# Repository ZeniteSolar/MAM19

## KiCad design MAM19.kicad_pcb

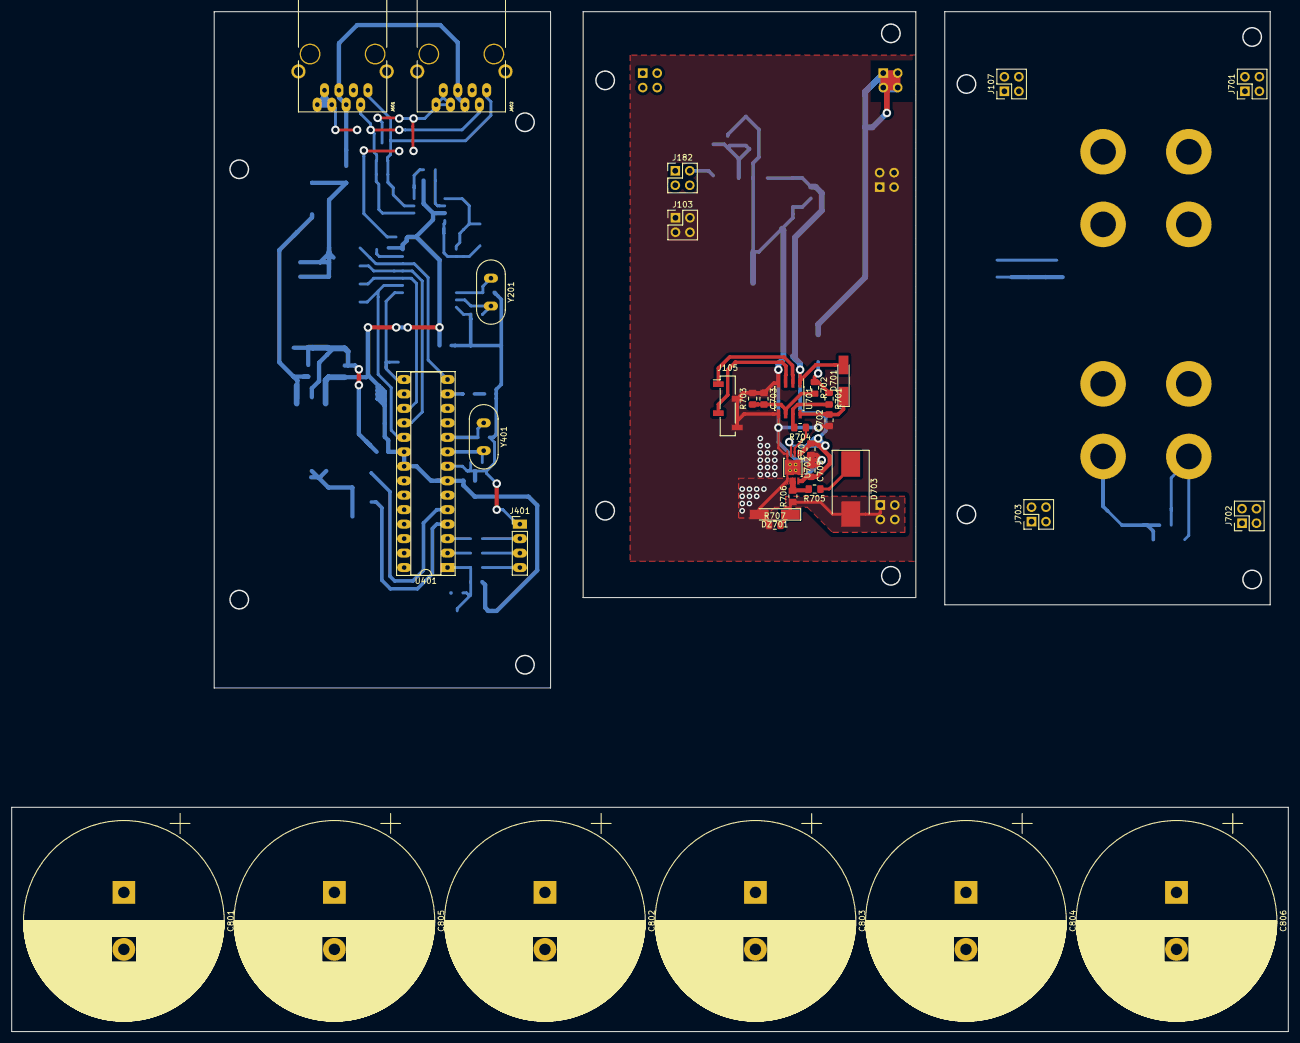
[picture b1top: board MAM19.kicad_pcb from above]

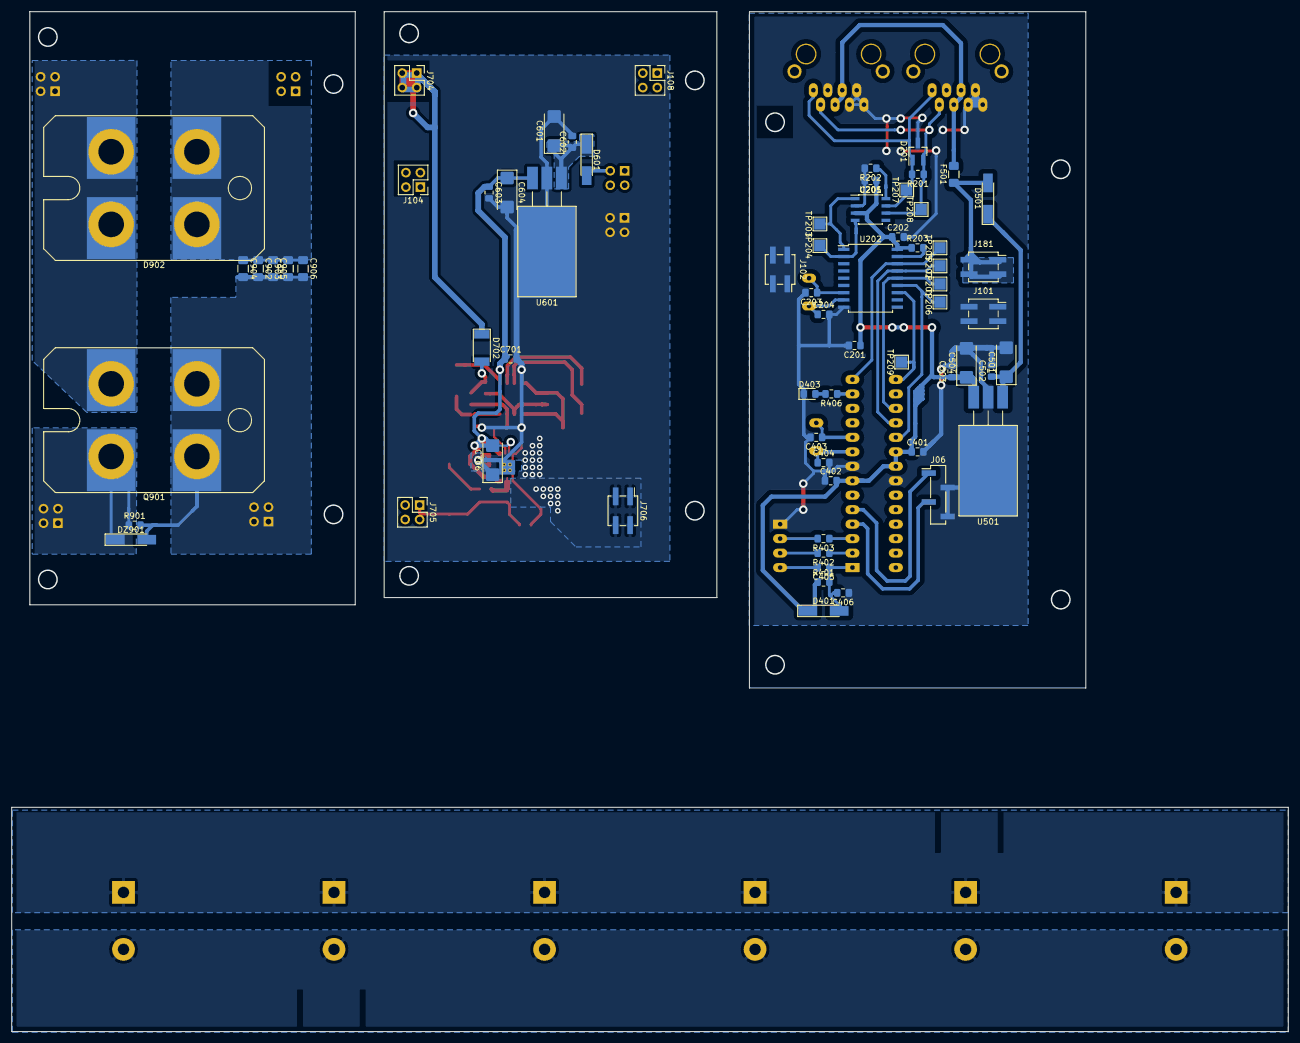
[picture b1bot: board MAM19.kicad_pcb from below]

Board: 2 copper layers, 224.2 x 179.1 mm, 101 parts (66 on the bottom side), 45 nets.

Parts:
C201, C202, C205, C401, C402, C405, C406, C502, C503, C602, C603, C701, C702, C703, C704: 100nF; C_0805_2012Metric_Pad1.15x1.40mm_HandSolder
C203, C204, C403, C404: 22pF; C_0805_2012Metric_Pad1.15x1.40mm_HandSolder
C501, C504, C601, C604: 1uF; CP_EIA-6032-20_AVX-F_Pad2.25x2.35mm_HandSolder
C705: 1uF; C_0805_2012Metric_Pad1.15x1.40mm_HandSolder
C706: 10uF; CP_EIA-6032-20_AVX-F_Pad2.25x2.35mm_HandSolder
C801, C802, C803, C804, C805, C806: 4700uF; CP_Radial_D35.0mm_P10.00mm_SnapIn
C902, C903, C904, C905, C906: 10nF 250V; C_1206_3216Metric_Pad1.42x1.75mm_HandSolder
D201: pesd1can; SOT-23_Handsoldering
D401, D501, D601: LL4148; D_MiniMELF_Handsoldering
D403: LED_RED; LED_0805_2012Metric_Pad1.15x1.40mm_HandSolder
D701: BAV102; D_MiniMELF_Handsoldering
D702: BYD77; D_MELF
D703: ES3B; D_SMC_Handsoldering
D902: DSEI2x101; SOT-227
DZ701, DZ901: 15V; D_MiniMELF_Handsoldering
F501: 500mA; Fuse_1206_3216Metric_Pad1.42x1.75mm_HandSolder
J06: PWM/IR C; PinHeader_1x04_P2.54mm_Vertical_SMD_Pin1Left
J101: GNDC1; PinSocket_2x02_P2.54mm_Vertical_SMD
J102: GNDC2; PinSocket_2x02_P2.54mm_Vertical_SMD
J103: GNDD1; PinHeader_2x02_P2.54mm_Vertical
J104: GNDD2; PinHeader_2x02_P2.54mm_Vertical
J105: PWM/IR D; PinSocket_1x04_P2.54mm_Vertical_SMD_Pin1Left
J107: HOLD1; PinHeader_2x02_P2.54mm_Vertical
J108: HOLD2; PinHeader_2x02_P2.54mm_Vertical
J181: +18C; PinSocket_2x02_P2.54mm_Vertical_SMD
J182: +18D; PinHeader_2x02_P2.54mm_Vertical
J401: USART; PinHeader_1x04_P2.54mm_Vertical
J601, J602: RJ45; RJ45_YH59_01
J701: DRAIND; PinHeader_2x02_P2.54mm_Vertical
J702: GATED; PinHeader_2x02_P2.54mm_Vertical
J703: SOURCED; PinHeader_2x02_P2.54mm_Vertical
J704: DRAINCH; PinHeader_2x02_P2.54mm_Vertical
J705: GATECH; PinHeader_2x02_P2.54mm_Vertical
J706: SOURCECH; PinHeader_2x02_P2.54mm_Vertical_SMD
Q901: IXFN420N10T; SOT-227
R201: 120; R_0805_2012Metric_Pad1.15x1.40mm_HandSolder
R202: 4k7; R_0805_2012Metric_Pad1.15x1.40mm_HandSolder
R203, R401: 10k; R_0805_2012Metric_Pad1.15x1.40mm_HandSolder
R402, R403: 1k; R_0805_2012Metric_Pad1.15x1.40mm_HandSolder
R406: 330; R_0805_2012Metric_Pad1.15x1.40mm_HandSolder
R701: 22K; R_0805_2012Metric_Pad1.15x1.40mm_HandSolder
R702, R707, R901: 10K; R_0805_2012Metric_Pad1.15x1.40mm_HandSolder
R703: 820; R_0805_2012Metric_Pad1.15x1.40mm_HandSolder
R704: 0; R_0805_2012Metric_Pad1.15x1.40mm_HandSolder
R705: 4R7; R_0805_2012Metric_Pad1.15x1.40mm_HandSolder
R706: 10; R_0805_2012Metric_Pad1.15x1.40mm_HandSolder
TP201: SI; TestPoint_Pad_2.0x2.0mm
TP202: SO; TestPoint_Pad_2.0x2.0mm
TP203: TXCAN; TestPoint_Pad_2.0x2.0mm
TP204: RXCAN; TestPoint_Pad_2.0x2.0mm
TP205: SC; TestPoint_Pad_2.0x2.0mm
TP206: SCK; TestPoint_Pad_2.0x2.0mm
TP207: CAN_H; TestPoint_Pad_2.0x2.0mm
TP208: CAN_L; TestPoint_Pad_2.0x2.0mm
TP209: INT; TestPoint_Pad_2.0x2.0mm
U201: MCP2551-I/SN; SOIC-8_3.9x4.9mm_P1.27mm
U202: MCP2515-xSO; SOIC-18W_7.5x11.6mm_P1.27mm
U401: ATMEGA328P-PU; DIP-28_W7.62mm_Socket
U501: LM7805; TO-220-3_Horizontal_TabDown_SMD
U601: LM7815; TO-220-3_Horizontal_TabDown_SMD
U701: IR2127S; SOIC-8_3.9x4.9mm_P1.27mm
U702: UCC2732; MSOP-8-1EP_3x3mm_P0.65mm_EP2.54x2.8mm_ThermalVias
Y201, Y401: 16MHz; Crystal_HC49-U_Vertical

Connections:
+5V: C201.1, C202.1, C205.1, C401.1, C402.2, C503.1, C504.1, D401.1, R203.1, R401.1, U201.3, U202.18, U401.7, U401.20, U401.21, U501.3
+15V: C603.1, C604.1, C701.1, C704.2, C705.2, C706.2, D701.2, U601.3, U701.1, U702.1, U702.3, U702.8
+36V: C801.1, C802.1, C803.1, C804.1, C805.1, C806.1, C902.1, C903.2, C904.1, C905.1, C906.1, D902.1, D902.4
/CANBUS CONN/CAN_18V: F501.2, J601.4, J601.5, J602.4, J602.5
/CANBUS CONN/CAN_H: D201.1, J601.1, J602.1, R201.2, TP207.1, U201.7
/CANBUS CONN/CAN_L: D201.2, J601.2, J602.2, R201.1, TP208.1, U201.6
/CANBUS/CS: TP205.1, U202.16, U401.14
/CANBUS/INT: TP209.1, U202.12, U401.15
/CANBUS/RXCAN: TP204.1, U201.4, U202.2
/CANBUS/TXCAN: TP203.1, U201.1, U202.1
/MCU/IR_2127_FAULT: J06.3, U401.4
/MCU/PWM: J06.1, U401.5
/MCU/RESET: C405.1, C406.2, D401.2, R401.2, U401.1
/MCU/USART_RX: R402.1, U401.2
/MCU/USART_TX: R403.1, U401.3
/MISO: TP202.1, U202.15, U401.18
/MOSI: TP201.1, U202.14, U401.17
/POWER SUPPLY +15V/+18V_IN: D501.2, D601.2, F501.1, J181.1, J181.2, J181.3, J181.4, J182.1, J182.2, J182.3, J182.4
/SCK: TP206.1, U202.13, U401.19
/chopper/-MOTOR: D702.1, D902.2, D902.3, J701.1, J701.2, J701.3, J701.4, J704.1, J704.2, J704.3, J704.4, Q901.3
/chopper/GATE: D703.2, DZ701.1, DZ901.1, J702.1, J702.2, J702.3, J702.4, J705.1, J705.2, J705.3, J705.4, Q901.2, R706.1, R707.2, R901.1
/driver/IR2127_FAULT: J105.3, U701.3
/driver/PWM: J105.1, U701.2
GND: C201.2, C202.2, C203.2, C204.2, C205.2, C401.2, C402.1, C403.2, C404.2, C406.1, C501.2, C502.2, C503.2, C504.2, C601.2, C602.2, C603.2, C604.2, C701.2, C702.1, C703.1, C704.1, C705.1, C706.1, C801.2, C802.2, C803.2, C804.2, C805.2, C806.2, C902.2, C903.1, C904.2, C905.2, C906.2, D201.3, D403.1, DZ701.2, DZ901.2, J06.2, J06.4, J101.1, J101.2, J101.3, J101.4, J102.1, J102.2, J102.3, J102.4, J103.1, J103.2, J103.3, J103.4, J104.1, J104.2, J104.3, J104.4, J105.2, J105.4, J401.1, J601.3, J601.6, J601.7, J601.8, J602.3, J602.6, J602.7, J602.8, J703.1, J703.2, J703.3, J703.4, J706.1, J706.2, J706.3, J706.4, Q901.1, Q901.4, R202.2, R703.2, R707.1, R901.2, U201.2, U202.9, U401.8, U401.22, U501.2, U601.2, U701.4, U701.5, U702.4, U702.5
unnamed: C203.1, U202.7, Y201.1
unnamed: C204.1, U202.8, Y201.2
unnamed: C403.1, U401.10, Y401.1
unnamed: C404.1, U401.9, Y401.2
unnamed: C405.2, J401.4
unnamed: C501.1, C502.1, D501.1, U501.1
unnamed: C601.1, C602.1, D601.1, U601.1
unnamed: C702.2, D701.1, U701.8
unnamed: C703.2, R702.2, R703.1, U701.6
unnamed: D403.2, R406.2
unnamed: D702.2, R701.1, R702.1
unnamed: D703.1, R705.1
unnamed: J107.1, J107.2, J107.3, J107.4, J108.1, J108.2, J108.3, J108.4
unnamed: J401.2, R403.2
unnamed: J401.3, R402.2
unnamed: R202.1, U201.8
unnamed: R203.2, U202.17
unnamed: R406.1, U401.13
unnamed: R701.2, R704.2, U701.7
unnamed: R704.1, U702.2
unnamed: R705.2, R706.2, U702.6, U702.7

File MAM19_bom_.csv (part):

Component,Description,Part,References,Value,Footprint,Quantity Per PCB,Datasheet
1,"Unpolarized capacitor, small symbol",C_Small,C201 C202 C205 C401 C402 C405 C406 C502 C503 C602 C603 C701 C702 C703 C704,100nF,C_0805_2012Metric_Pad1.15x1.40mm_HandSolder,15,
2,"Unpolarized capacitor, small symbol",C_Small,C902 C903 C904 C905 C906,10nF 250V,C_1206_3216Metric_Pad1.42x1.75mm_HandSolder,5,~
3,"Unpolarized capacitor, small symbol",C_Small,C706,10uF,CP_EIA-6032-20_AVX-F_Pad2.25x2.35mm_HandSolder,1,~
4,"Polarized capacitor, small US symbol",CP1_Small,C501 C504 C601 C604,1uF,CP_EIA-6032-20_AVX-F_Pad2.25x2.35mm_HandSolder,4,
5,"Unpolarized capacitor, small symbol",C_Small,C705,1uF,C_0805_2012Metric_Pad1.15x1.40mm_HandSolder,1,~
6,"Unpolarized capacitor, small symbol",C_Small,C203 C204 C403 C404,22pF,C_0805_2012Metric_Pad1.15x1.40mm_HandSolder,4,
7,"Unpolarized capacitor, small symbol",C_Small,C801 C802 C803 C804 C805 C806,4700uF,CP_Radial_D35.0mm_P10.00mm_SnapIn,6,~
8,"Diode, small symbol",D_Small,D701,BAV102,D_MiniMELF_Handsoldering,1,~
9,"Diode, small symbol",D_Small,D702,BYD77,D_MELF,1,~
10,,DSEI2x101-Diode,D902,DSEI2x101,SOT-227,1,
11,"Diode, small symbol",D_Small,D703,ES3B,D_SMC_Handsoldering,1,~
12,"Light emitting diode, small symbol",LED_Small,D403,LED_RED,LED_0805_2012Metric_Pad1.15x1.40mm_HandSolder,1,
13,"100V 0.15A standard switching diode, MiniMELF",LL4148,D401 D501 D601,LL4148,D_MiniMELF_Handsoldering,3,http://www.vishay.com/docs/85557/ll4148.pdf
14,"Bidirectional dual transient-voltage-suppression diode, center on pin 3",D_TVS_x2_AAC,D201,pesd1can,SOT-23_Handsoldering,1,https://assets.nexperia.com/documents/data-sheet/PESD1CAN.pdf
15,"Zener diode, small symbol",D_Zener_Small,DZ701 DZ901,15V,D_MiniMELF_Handsoldering,2,~
16,"Fuse, small symbol",Fuse_Small,F501,500mA,Fuse_1206_3216Metric_Pad1.42x1.75mm_HandSolder,1,~
17,"Generic connector, double row, 02x02, counter clockwise pin numbering scheme (similar to DIP packge numbering), script generated (kicad-library-utils/schlib/autogen/connector/)",Conn_02x02_Counter_Clockwise,J181,+18C,PinSocket_2x02_P2.54mm_Vertical_SMD,1,~
18,"Generic connector, double row, 02x02, counter clockwise pin numbering scheme (similar to DIP packge numbering), script generated (kicad-library-utils/schlib/autogen/connector/)",Conn_02x02_Counter_Clockwise,J182,+18D,PinHeader_2x02_P2.54mm_Vertical,1,~
19,"Generic connector, double row, 02x02, counter clockwise pin numbering scheme (similar to DIP packge numbering), script generated (kicad-library-utils/schlib/autogen/connector/)",Conn_02x02_Counter_Clockwise,J704,DRAINCH,PinHeader_2x02_P2.54mm_Vertical,1,~
20,"Generic connector, double row, 02x02, counter clockwise pin numbering scheme (similar to DIP packge numbering), script generated (kicad-library-utils/schlib/autogen/connector/)",Conn_02x02_Counter_Clockwise,J701,DRAIND,PinHeader_2x02_P2.54mm_Vertical,1,~
21,"Generic connector, double row, 02x02, counter clockwise pin numbering scheme (similar to DIP packge numbering), script generated (kicad-library-utils/schlib/autogen/connector/)",Conn_02x02_Counter_Clockwise,J705,GATECH,PinHeader_2x02_P2.54mm_Vertical,1,~
22,"Generic connector, double row, 02x02, counter clockwise pin numbering scheme (similar to DIP packge numbering), script generated (kicad-library-utils/schlib/autogen/connector/)",Conn_02x02_Counter_Clockwise,J702,GATED,PinHeader_2x02_P2.54mm_Vertical,1,~
23,"Generic connector, double row, 02x02, counter clockwise pin numbering scheme (similar to DIP packge numbering), script generated (kicad-library-utils/schlib/autogen/connector/)",Conn_02x02_Counter_Clockwise,J101,GNDC1,PinSocket_2x02_P2.54mm_Vertical_SMD,1,~
24,"Generic connector, double row, 02x02, counter clockwise pin numbering scheme (similar to DIP packge numbering), script generated (kicad-library-utils/schlib/autogen/connector/)",Conn_02x02_Counter_Clockwise,J102,GNDC2,PinSocket_2x02_P2.54mm_Vertical_SMD,1,~
25,"Generic connector, double row, 02x02, counter clockwise pin numbering scheme (similar to DIP packge numbering), script generated (kicad-library-utils/schlib/autogen/connector/)",Conn_02x02_Counter_Clockwise,J103,GNDD1,PinHeader_2x02_P2.54mm_Vertical,1,~
26,"Generic connector, double row, 02x02, counter clockwise pin numbering scheme (similar to DIP packge numbering), script generated (kicad-library-utils/schlib/autogen/connector/)",Conn_02x02_Counter_Clockwise,J104,GNDD2,PinHeader_2x02_P2.54mm_Vertical,1,~
27,"Generic connector, double row, 02x02, counter clockwise pin numbering scheme (similar to DIP packge numbering), script generated (kicad-library-utils/schlib/autogen/connector/)",Conn_02x02_Counter_Clockwise,J107,HOLD1,PinHeader_2x02_P2.54mm_Vertical,1,~
28,"Generic connector, double row, 02x02, counter clockwise pin numbering scheme (similar to DIP packge numbering), script generated (kicad-library-utils/schlib/autogen/connector/)",Conn_02x02_Counter_Clockwise,J108,HOLD2,PinHeader_2x02_P2.54mm_Vertical,1,~
29,"Generic screw terminal, single row, 01x04, script generated (kicad-library-utils/schlib/autogen/connector/)",Screw_Terminal_01x04,J06,PWM/IR C,PinHeader_1x04_P2.54mm_Vertical_SMD_Pin1Left,1,~
30,"Generic screw terminal, single row, 01x04, script generated (kicad-library-utils/schlib/autogen/connector/)",Screw_Terminal_01x04,J105,PWM/IR D,PinSocket_1x04_P2.54mm_Vertical_SMD_Pin1Left,1,~
31,"RJ connector, 8P8C (8 positions 8 connected), RJ31/RJ32/RJ33/RJ34/RJ35/RJ41/RJ45/RJ49/RJ61, Shielded",RJ45_Shielded,J601 J602,RJ45,RJ45_YH59_01,2,
32,"Generic connector, double row, 02x02, counter clockwise pin numbering scheme (similar to DIP packge numbering), script generated (kicad-library-utils/schlib/autogen/connector/)",Conn_02x02_Counter_Clockwise,J706,SOURCECH,PinHeader_2x02_P2.54mm_Vertical_SMD,1,~
33,"Generic connector, double row, 02x02, counter clockwise pin numbering scheme (similar to DIP packge numbering), script generated (kicad-library-utils/schlib/autogen/connector/)",Conn_02x02_Counter_Clockwise,J703,SOURCED,PinHeader_2x02_P2.54mm_Vertical,1,~
34,"Generic connector, single row, 01x04, script generated (kicad-library-utils/schlib/autogen/connector/)",Conn_01x04,J401,USART,PinHeader_1x04_P2.54mm_Vertical,1,~
35,,IXFN420N10T-Transistor_FET,Q901,IXFN420N10T,SOT-227,1,
36,"Resistor, small symbol",R_Small,R704,0,R_0805_2012Metric_Pad1.15x1.40mm_HandSolder,1,~
37,"Resistor, small symbol",R_Small,R706,10,R_0805_2012Metric_Pad1.15x1.40mm_HandSolder,1,~
38,"Resistor, small symbol",R_Small,R203 R401 R702 R707 R901,10k,R_0805_2012Metric_Pad1.15x1.40mm_HandSolder,5,
39,"Resistor, small symbol",R_Small,R201,120,R_0805_2012Metric_Pad1.15x1.40mm_HandSolder,1,
40,"Resistor, small symbol",R_Small,R402 R403,1k,R_0805_2012Metric_Pad1.15x1.40mm_HandSolder,2,
41,"Resistor, small symbol",R_Small,R701,22K,R_0805_2012Metric_Pad1.15x1.40mm_HandSolder,1,~
42,"Resistor, small symbol",R_Small,R406,330,R_0805_2012Metric_Pad1.15x1.40mm_HandSolder,1,~
43,"Resistor, small symbol",R_Small,R705,4R7,R_0805_2012Metric_Pad1.15x1.40mm_HandSolder,1,~
44,"Resistor, small symbol",R_Small,R202,4k7,R_0805_2012Metric_Pad1.15x1.40mm_HandSolder,1,
45,"Resistor, small symbol",R_Small,R703,820,R_0805_2012Metric_Pad1.15x1.40mm_HandSolder,1,~
46,"10MHz, 4kB Flash, 512B SRAM, 256B EEPROM, DIP-28",ATmega328P-PU,U401,ATMEGA328P-PU,DIP-28_W7.62mm_Socket,1,http://ww1.microchip.com/downloads/en/DeviceDoc/Atmel-8025-8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
47,,IR2127S-Sensor_Current,U701,IR2127S,SOIC-8_3.9x4.9mm_P1.27mm,1,
48,"Positive 1A 35V Linear Regulator, Fixed Output 5V, TO-220",LM7805_TO220,U501,LM7805,TO-220-3_Horizontal_TabDown_SMD,1,https://www.sparkfun.com/datasheets/Components/LM7805.pdf
49,"Positive 1A 35V Linear Regulator, Fixed Output 5V, TO-220",LM7805_TO220,U601,LM7815,TO-220-3_Horizontal_TabDown_SMD,1,https://www.sparkfun.com/datasheets/Components/LM7805.pdf
50,"Stand-Alone CAN Controller with SPI Interface, SOIC-18",MCP2515-xSO,U202,MCP2515-xSO,SOIC-18W_7.5x11.6mm_P1.27mm,1,http://ww1.microchip.com/downloads/en/DeviceDoc/21801e.pdf
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
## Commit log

2019-06-19 muita coisa
2019-08-01 Componentes TUDO
2019-09-26 Mosfet driver PCB
2019-09-26 small updates driver Mosfet
2019-09-26 diagrama adicionado
2019-11-27 Driver layout and snubber
2019-12-05 connectors moved
2020-01-07 Driver Panel
2020-01-08 pinos pwm e fault alterados de acordo com o sugerido em #1
2020-01-08 panels generated and pdfs exported
2020-01-08 cleaned
2020-01-08 Rename imprimir.mk to imprimir.md
2020-01-08 BOM added
